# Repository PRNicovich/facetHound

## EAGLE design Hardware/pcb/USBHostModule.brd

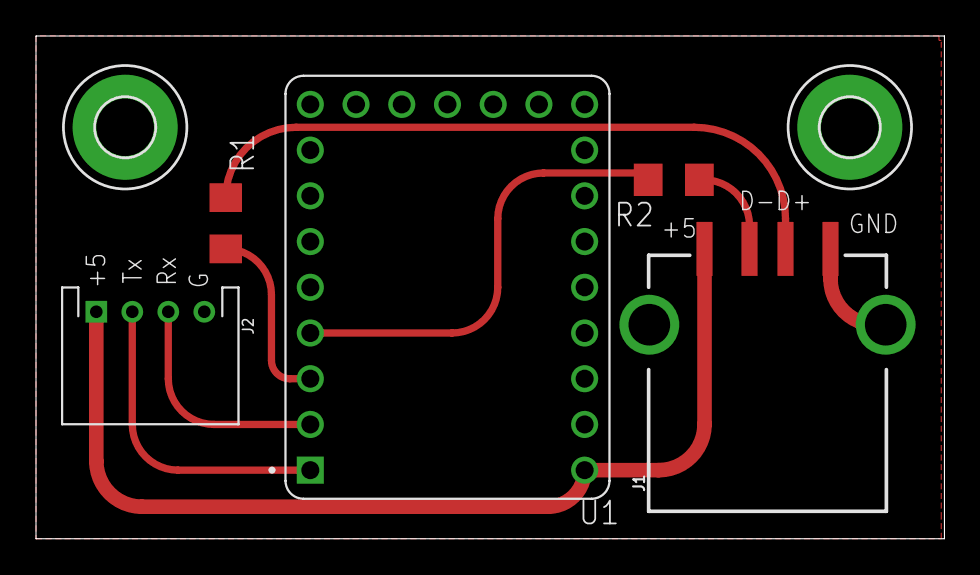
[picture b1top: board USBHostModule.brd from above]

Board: 2 copper layers, 50.5 x 27.9 mm, 7 parts (0 on the bottom side), 8 nets.

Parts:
H1, H4: MOUNT-PAD-ROUND3.2; 3,2-PAD
J1: USB_A_SMT_FEMALE; USB-A-S-SILK-FEMALE
J2: JST-PH-4_TH-RA; S4B-PH-KL
R1, R2: 22R; R1206
U1: RP2040-ZERO'; MODULE_RP2040-ZERO

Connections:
+5: J1.VBUS, J2.1, U1.23
D+: J1.D+, R1.1
D-: J1.D-, R2.1
GND: H1.B3,2, H4.B3,2, J1.GND, J1.SHLD1, J1.SHLD2, J2.4, U1.22
unnamed: R2.2, U1.4
unnamed: R1.2, U1.3
RX: J2.3, U1.2
TX: J2.2, U1.1

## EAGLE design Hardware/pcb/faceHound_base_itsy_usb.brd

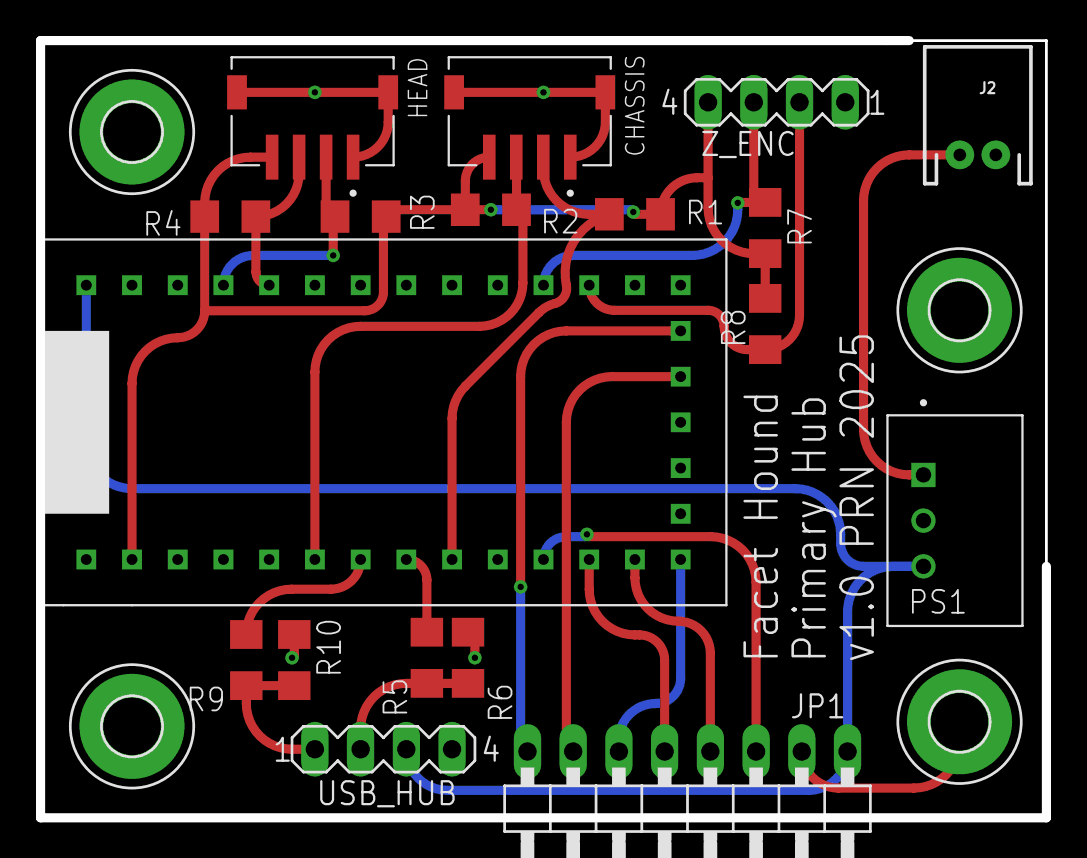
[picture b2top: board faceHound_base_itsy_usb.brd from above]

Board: 2 copper layers, 55.9 x 43.2 mm, 22 parts (0 on the bottom side), 21 nets.

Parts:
CHASSIS: S4B-ZR-SM4A-TF(LF)(SN); JST_S4B-ZR-SM4A-TF(LF)(SN)
H1, H2, H3, H4: MOUNT-PAD-ROUND3.2; 3,2-PAD
HEAD: S4B-ZR-SM4A-TF(LF)(SN); JST_S4B-ZR-SM4A-TF(LF)(SN)
J2: JST-2-PTH
JP1: 1X08/90
PS1: TSR_1-2450; CONV_TSR_1-2450
R1, R2, R3, R4, R7, R8: R1206
R5, R9: 4k7; R1206
R6, R10: 10k; R1206
U$1: ITSYBITSY_M4
USB_HUB: MA04-1
Z_ENC: MA04-1

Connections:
GND: H1.B3,2, H2.B3,2, H3.B3,2, H4.B3,2, HEAD.1, HEAD.S1, HEAD.S2, J2.2, JP1.2, PS1.2, R6.2, R10.1, U$1.P$32, USB_HUB.4, Z_ENC.1
unnamed: JP1.3, U$1.P$11
unnamed: R9.2, R10.2, USB_HUB.1
unnamed: R5.2, R6.1, USB_HUB.2
unnamed: JP1.1, PS1.3, U$1.P$33, USB_HUB.3
unnamed: CHASSIS.1, CHASSIS.S1, CHASSIS.S2
unnamed: JP1.5, U$1.P$12
unnamed: JP1.4, U$1.P$13
unnamed: CHASSIS.4, HEAD.4, R1.1, R2.1, R3.1, R4.1, R7.1, R8.2, U$1.P$2, Z_ENC.4
unnamed: JP1.6, U$1.P$14
unnamed: JP1.8, U$1.P$19
unnamed: JP1.7, U$1.P$18
unnamed: CHASSIS.2, R1.2, U$1.P$9
unnamed: CHASSIS.3, R2.2, U$1.P$6
unnamed: HEAD.2, R3.2, U$1.P$30
unnamed: HEAD.3, R4.2, U$1.P$29
unnamed: R9.1, U$1.P$7
unnamed: R5.1, U$1.P$8
unnamed: R8.1, U$1.P$22, Z_ENC.2
unnamed: R7.2, U$1.P$23, Z_ENC.3
unnamed: J2.1, PS1.1

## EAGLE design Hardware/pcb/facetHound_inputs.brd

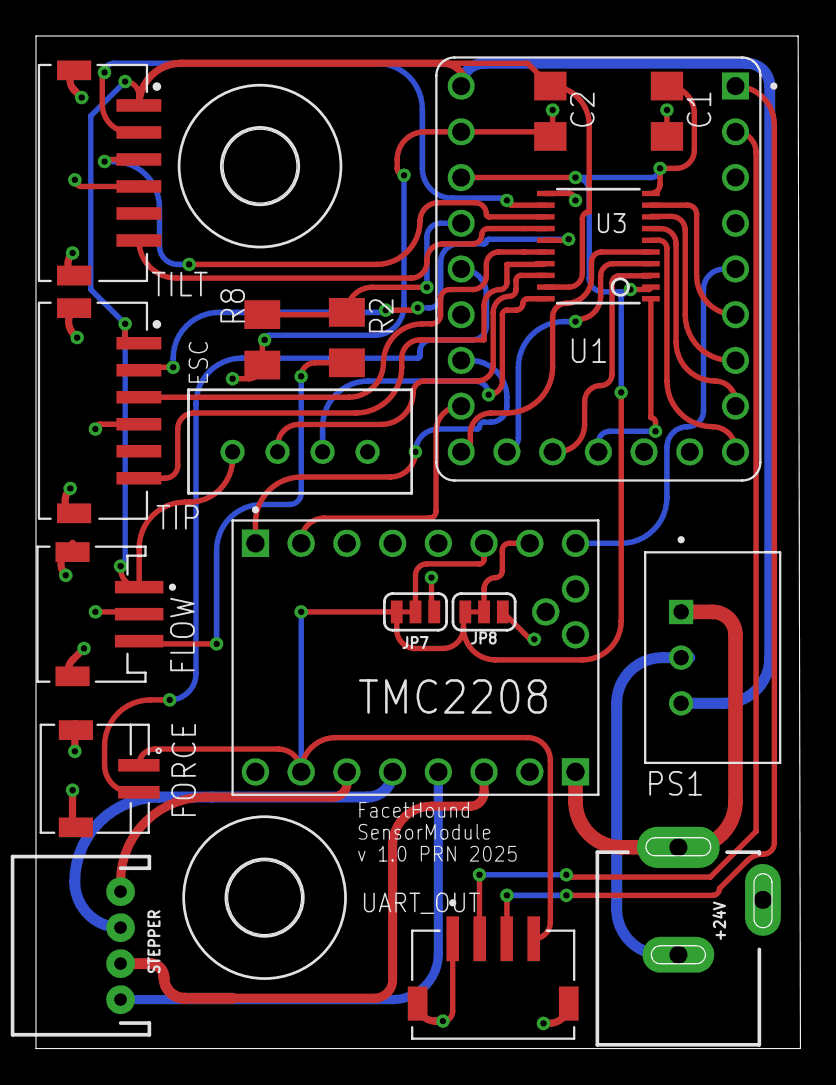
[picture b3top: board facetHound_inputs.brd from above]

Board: 2 copper layers, 42.5 x 56.2 mm, 20 parts (0 on the bottom side), 35 nets.

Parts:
+24V: POWER_JACKPOWER_JACK_SLOT; POWER_JACK_PTH_SLOT
C1, C2: 0.1uF; C1206
ESC: B4B-XH-A
FLOW: S3B-ZR-SM4A-TF; JST_S3B-ZR-SM4A-TF
FORCE: S2B-ZR-SM4A-TF; JST_S2B-ZR-SM4A-TF
H1, H2: MOUNT-HOLE4.1; 4,1
JP7, JP8: JUMPER-SMT_3_1-NC_TRACE_SILK; SMT-JUMPER_3_1-NC_TRACE_SILK
PS1: TSR_1-2450; CONV_TSR_1-2450
R2, R8: 10k; M1206
STEPPER: JST-4-PTH
TILT: S6B-ZR-SM4A-TF(LF)(SN); JST_S6B-ZR-SM4A-TF(LF)(SN)
TIP: S6B-ZR-SM4A-TF(LF)(SN); JST_S6B-ZR-SM4A-TF(LF)(SN)
TMC2208: TMC2208_SILENTSTEPSTICK; MODULE_TMC2208_SILENTSTEPSTICK
U1: RP2040-ZERO'; MODULE_RP2040-ZERO
U3: TSSOP20
UART_OUT: S4B-ZR-SM4A-TF(LF)(SN); JST_S4B-ZR-SM4A-TF(LF)(SN)

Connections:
GND: C1.2, C2.2, ESC.4, FLOW.2, JP7.1, JP8.1, R8.1, TILT.4, TILT.SH1, TILT.SH2, TIP.4, TIP.SH1, TIP.SH2, TMC2208.JP2_2, TMC2208.JP2_8, U1.22, U3.11, UART_OUT.1, UART_OUT.S1, UART_OUT.S2
unnamed: R2.2, R8.2, U1.20
unnamed: FORCE.2, U1.19
unnamed: U1.2, UART_OUT.2
unnamed: U1.1, UART_OUT.3
unnamed: STEPPER.4, TMC2208.JP2_6
unnamed: TMC2208.JP1_2, U1.16
unnamed: C2.1, ESC.1, FLOW.1, PS1.3, TILT.1, TIP.1, U1.23, U3.19
unnamed: +24V.PWR, PS1.1, TMC2208.JP2_1
unnamed: +24V.GND, PS1.2
unnamed: STEPPER.3, TMC2208.JP2_5
unnamed: TMC2208.JP1_1, U1.17
unnamed: TMC2208.JP1_8, U1.5
unnamed: STEPPER.2, TMC2208.JP2_3
unnamed: C1.1, FORCE.1, JP7.3, JP8.3, TMC2208.JP2_7, U1.21, U3.2, U3.10, UART_OUT.4
unnamed: JP7.2, TMC2208.JP1_6
unnamed: FLOW.3, R2.1
unnamed: JP8.2, TMC2208.JP1_7
unnamed: STEPPER.1, TMC2208.JP2_4
unnamed: ESC.3, U3.20
unnamed: ESC.2, U3.18
unnamed: TIP.6, U3.17
unnamed: TIP.3, U3.16
unnamed: TIP.2, U3.15
unnamed: TILT.6, U3.14
unnamed: TILT.3, U3.13
unnamed: TILT.2, U3.12
unnamed: U1.12, U3.1
unnamed: U1.13, U3.3
unnamed: U1.14, U3.4
unnamed: U1.15, U3.5
unnamed: U1.6, U3.9
unnamed: U1.7, U3.8
unnamed: U1.8, U3.7
unnamed: U1.9, U3.6

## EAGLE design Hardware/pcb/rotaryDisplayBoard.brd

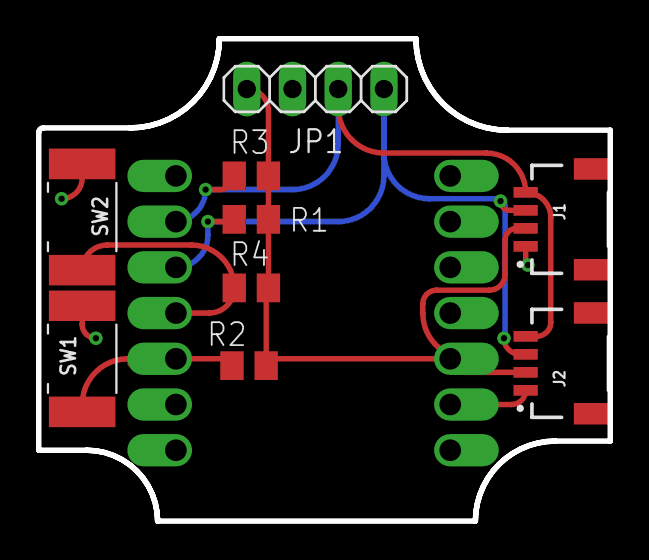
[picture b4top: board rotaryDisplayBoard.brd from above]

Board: 2 copper layers, 31.8 x 26.8 mm, 10 parts (1 on the bottom side), 6 nets.

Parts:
J1, J2: QWIIC_RIGHT_ANGLE; JST04_1MM_RA
JP1: 1X04
R1, R2, R3, R4: M0805
SW1, SW2: BTN_CK_KSS
U1: ADAFRUIT_QT_PY; MODULE_ADAFRUIT_QT_PY

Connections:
GND: J1.1, J2.1, JP1.2, SW1.P$1, SW2.P$1, U1.13
unnamed: J1.4, J2.4, JP1.3, R3.1, U1.6
unnamed: J1.3, J2.3, JP1.4, R4.1, U1.5
unnamed: J1.2, J2.2, JP1.1, R1.2, R2.2, R3.2, R4.2, U1.12
unnamed: R2.1, SW1.P$2, U1.3
unnamed: R1.1, SW2.P$2, U1.4

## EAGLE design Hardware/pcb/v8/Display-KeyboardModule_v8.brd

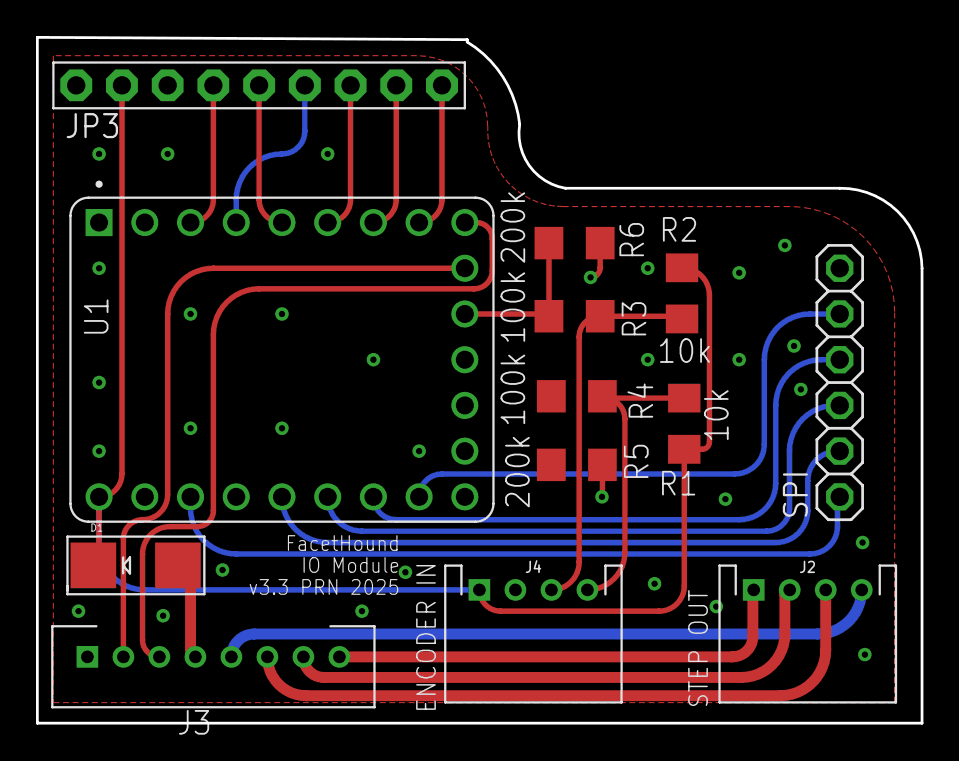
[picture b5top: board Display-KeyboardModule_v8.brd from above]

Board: 2 copper layers, 49.1 x 38.1 mm, 13 parts (0 on the bottom side), 24 nets.

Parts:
D1: SMADIODE
J2, J4: JST-PH-4_TH-RA; S4B-PH-KL
J3: B8B-PH-K-S
JP3: 1X09-BIG
R1, R2: 10k; R1206
R3, R4: 100k; R1206
R5, R6: 200k; R1206
SPI: 1X06
U1: RP2040-ZERO'; MODULE_RP2040-ZERO

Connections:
5V: D1.C, J4.1, JP3.2, R1.2, R2.2, U1.23
GND: J3.1, J4.2, JP3.1, R5.2, R6.2, SPI.6, U1.22
unnamed: D1.A, J3.4
unnamed: J2.1, J3.8
unnamed: JP3.4, U1.3
unnamed: J3.3, U1.9
unnamed: J3.2, U1.10
unnamed: JP3.6, U1.4
unnamed: JP3.5, U1.5
unnamed: JP3.7, U1.6
unnamed: JP3.8, U1.7
unnamed: JP3.9, U1.8
unnamed: SPI.2, U1.19
unnamed: J4.3, R2.1, R3.1
unnamed: J2.2, J3.7
unnamed: J2.3, J3.6
unnamed: J2.4, J3.5
unnamed: SPI.3, U1.18
unnamed: J4.4, R1.1, R4.1
unnamed: SPI.4, U1.17
unnamed: R3.2, R6.1, U1.11
unnamed: SPI.5, U1.16
unnamed: SPI.1, U1.21
unnamed: R4.2, R5.1, U1.12

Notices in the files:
parts and their libraries:
SparkFun-Connectors: Licensing: Creative Commons ShareAlike 4.0 International - https://creativecommons.org/licenses/by-sa/4.0
